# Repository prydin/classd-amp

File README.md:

# Class D Amplifier

Work in progress. Nothing to see here yet.

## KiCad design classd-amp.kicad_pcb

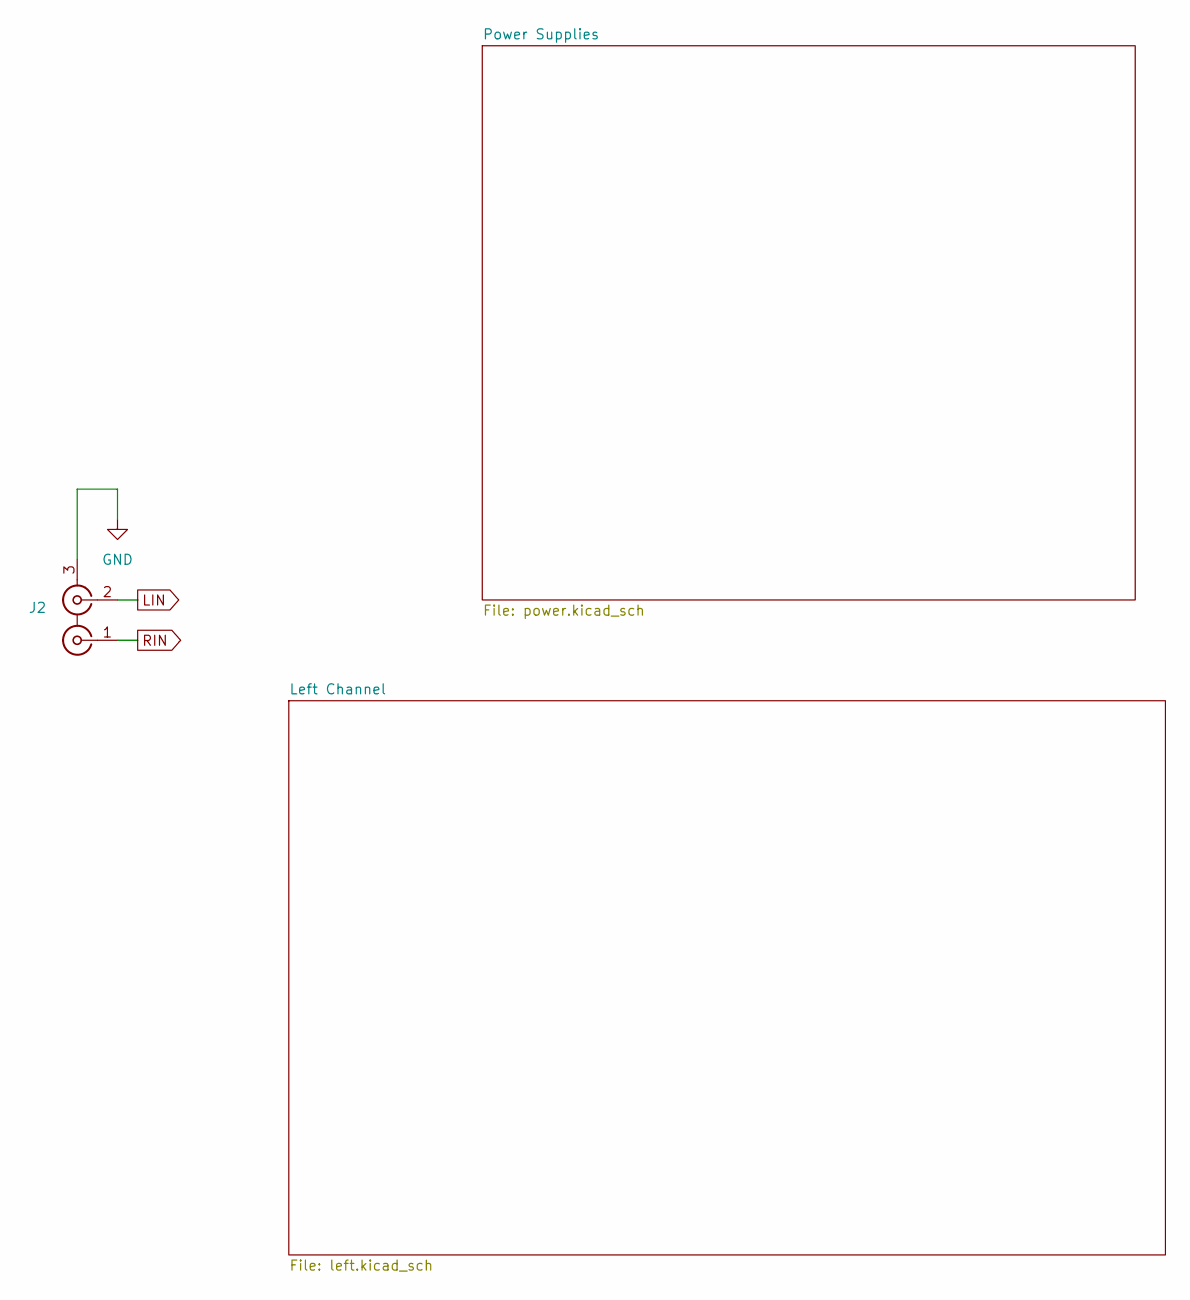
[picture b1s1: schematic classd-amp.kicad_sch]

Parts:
J2: Conn_Coaxial_x2; RCA_Stereo_Connector

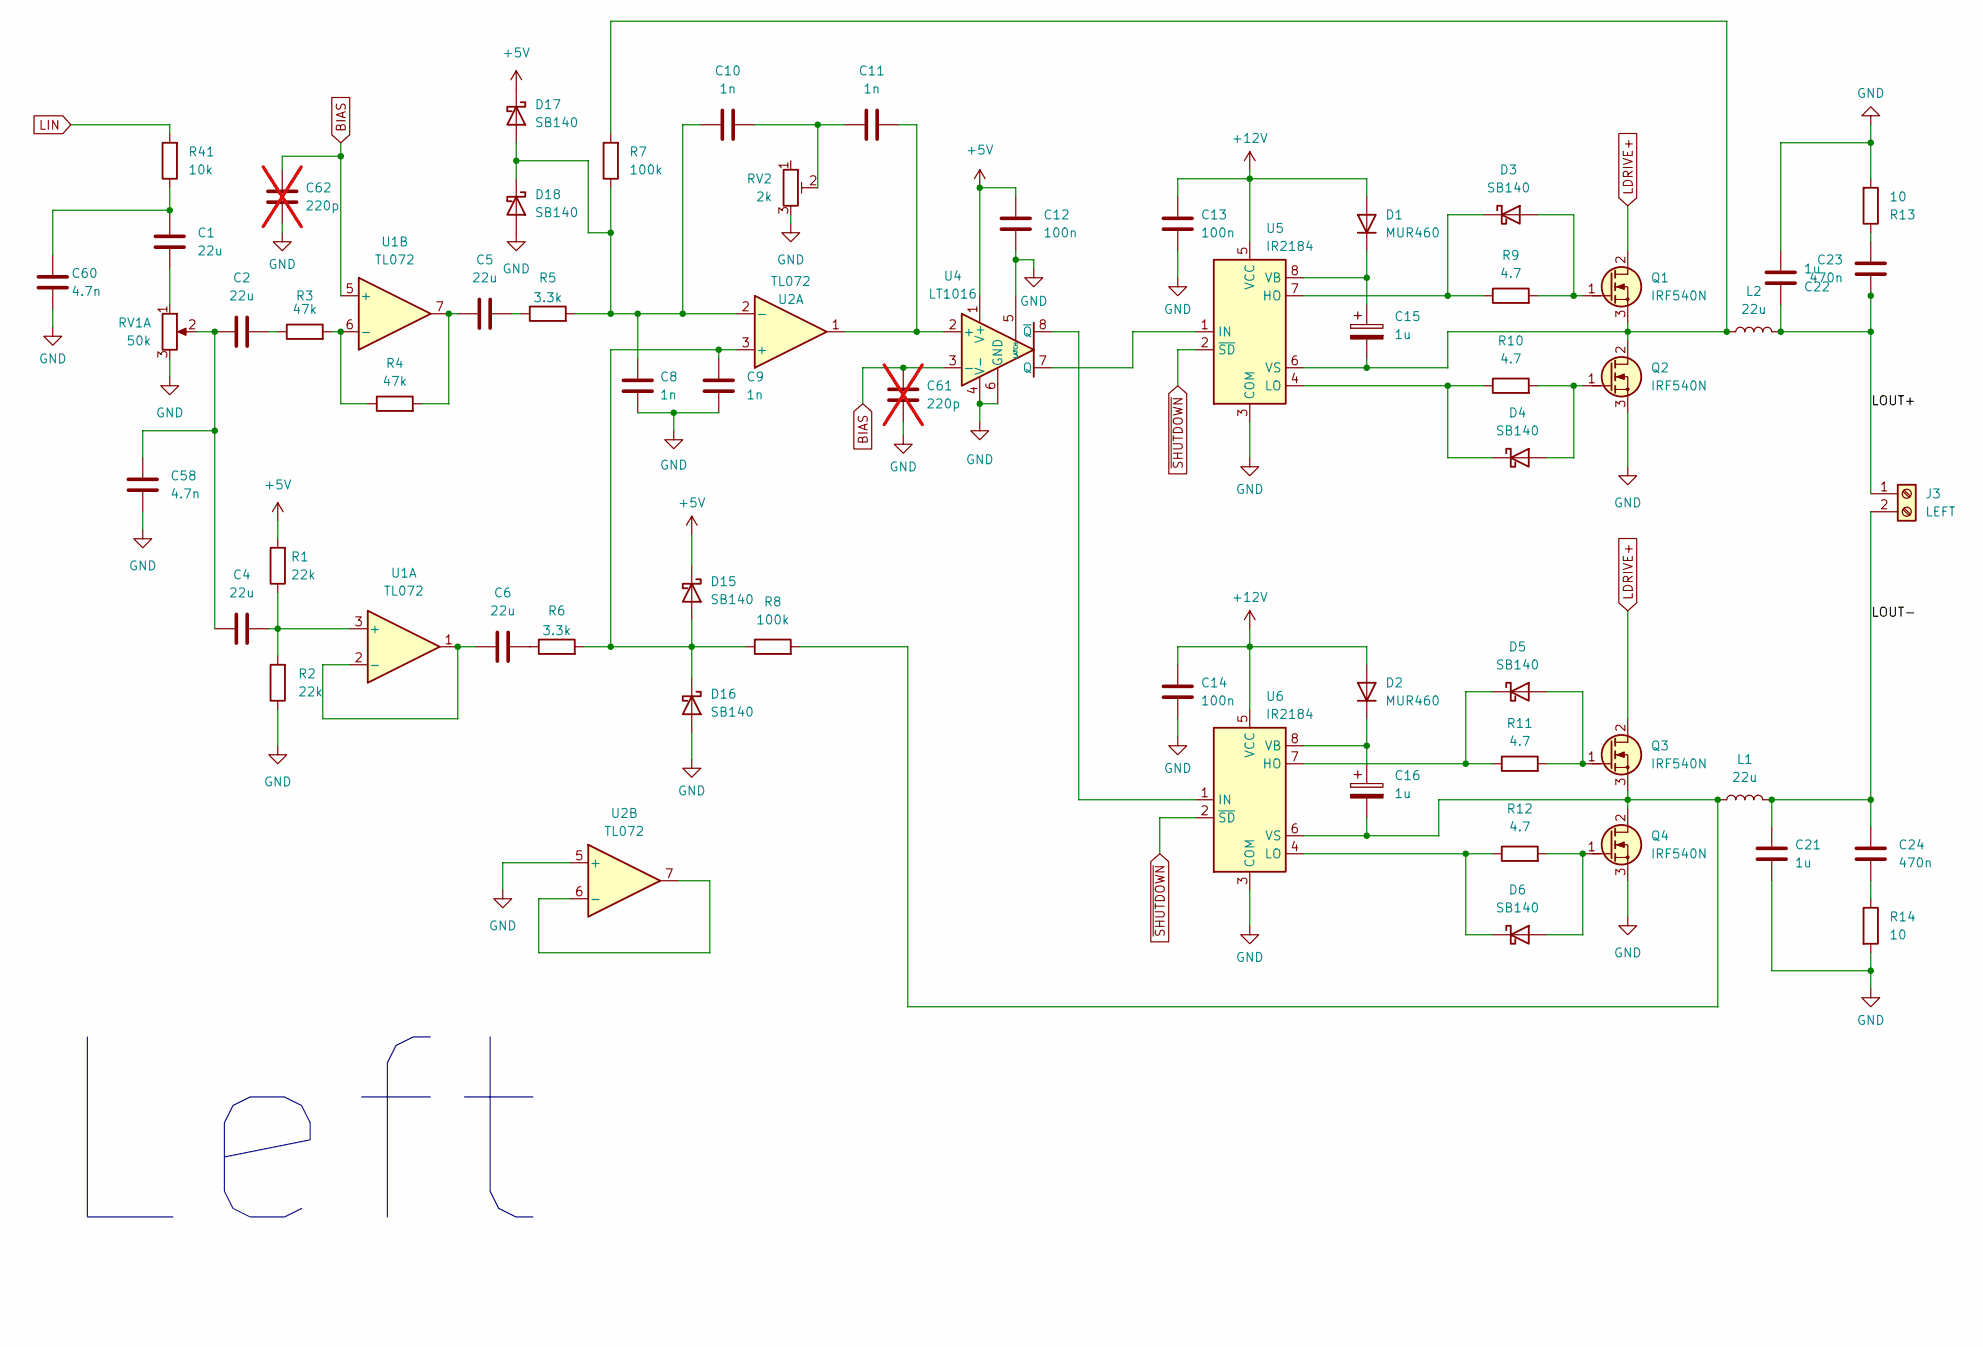
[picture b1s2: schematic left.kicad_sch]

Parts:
C1, C2, C4, C5, C6: 22u; CP_Radial_D8.0mm_P3.50mm
C8, C9, C10, C11: 1n; C_Disc_D4.7mm_W2.5mm_P5.00mm
C12, C13, C14: 100n; C_Disc_D3.4mm_W2.1mm_P2.50mm
C15, C16: 1u; CP_Radial_D4.0mm_P1.50mm
C21, C22: 1u; C_Rect_L18.0mm_W11.0mm_P15.00mm_FKS3_FKP3
C23, C24: 470n; C_Rect_L9.0mm_W3.8mm_P7.50mm_MKT
C58, C60: 4.7n; C_Disc_D3.4mm_W2.1mm_P2.50mm
C61, C62: 220p; C_Disc_D3.4mm_W2.1mm_P2.50mm; not fitted
D1, D2: MUR460; D_DO-41_SOD81_P10.16mm_Horizontal
D3, D4, D5, D6, D15, D16, D17, D18: SB140; D_DO-41_SOD81_P10.16mm_Horizontal
J3: LEFT; TerminalBlock_4Ucon_1x02_P3.50mm_Horizontal
L1, L2: 22u; L_Toroid_Vertical_L17.8mm_W8.1mm_P7.62mm_Bourns_5700
Q1, Q2, Q3, Q4: IRF540N; TO-220-3_Vertical
R1, R2: 22k; R_Axial_DIN0204_L3.6mm_D1.6mm_P7.62mm_Horizontal
R3, R4: 47k; R_Axial_DIN0204_L3.6mm_D1.6mm_P7.62mm_Horizontal
R5, R6: 3.3k; R_Axial_DIN0204_L3.6mm_D1.6mm_P7.62mm_Horizontal
R7, R8: 100k; R_Axial_DIN0204_L3.6mm_D1.6mm_P7.62mm_Horizontal
R9, R10, R11, R12: 4.7; R_Axial_DIN0204_L3.6mm_D1.6mm_P7.62mm_Horizontal
R13, R14: 10; R_Axial_DIN0614_L14.3mm_D5.7mm_P5.08mm_Vertical
R41: 10k; R_Axial_DIN0204_L3.6mm_D1.6mm_P7.62mm_Horizontal
RV1: 50k; PinHeader_1x03_P2.54mm_Vertical
RV2: 2k; Potentiometer_Runtron_RM-065_Vertical
U1, U2: TL072; DIP-8_W7.62mm_LongPads
U4: LT1016; DIP-8_W7.62mm_LongPads
U5, U6: IR2184; DIP-8_W7.62mm_LongPads

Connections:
+5V: C12.1, D15.1 (K), D17.1 (K), R1.2, U4.1 (V+); also elsewhere on the board
+12V: C13.1, C14.1, D1.2 (A), D2.2 (A), U5.5 (VCC), U6.5 (VCC); also elsewhere on the board
/Left Channel/LOUT+: C22.1, C23.1, J3.1, L2.2
/Left Channel/LOUT-: C21.1, C24.1, J3.2, L1.2
LDRIVE+: Q1.2 (D), Q3.2 (D); also elsewhere on the board
LIN: R41.2; also elsewhere on the board
unnamed: C1.1, C60.1, R41.1
unnamed: C1.2, RV1.1
unnamed: C2.1, R3.1
unnamed: C2.2, C4.2, C58.1, RV1.2
unnamed: C5.1, R4.2, U1.7
unnamed: C5.2, R5.1
unnamed: C6.2, R6.1
unnamed: C10.2, C11.1, RV2.2
unnamed: C23.2, R13.1
unnamed: C24.2, R14.1
unnamed: C15.1, D1.1 (K), U5.8 (VB)
unnamed: C16.1, D2.1 (K), U6.8 (VB)
unnamed: D3.2 (A), Q1.1 (G), R9.2
unnamed: D3.1 (K), R9.1, U5.7 (HO)
unnamed: D4.2 (A), Q2.1 (G), R10.2
unnamed: D4.1 (K), R10.1, U5.4 (LO)
unnamed: D5.2 (A), Q3.1 (G), R11.2
unnamed: D5.1 (K), R11.1, U6.7 (HO)
unnamed: D6.2 (A), Q4.1 (G), R12.2
unnamed: D6.1 (K), R12.1, U6.4 (LO)
unnamed: C9.1, D15.2 (A), D16.1 (K), R6.2, R8.1, U2.3 (+)
unnamed: C8.1, C10.1, D17.2 (A), D18.1 (K), R5.2, R7.1, U2.2 (-)
unnamed: C15.2, L2.1, Q1.3 (S), Q2.2 (D), R7.2, U5.6 (VS)
unnamed: C16.2, L1.1, Q3.3 (S), Q4.2 (D), R8.2, U6.6 (VS)
unnamed: C4.1, R1.1, R2.2, U1.3 (+)
unnamed: C6.1, U1.1, U1.2 (-)
unnamed: R3.2, R4.1, U1.6 (-)
unnamed: U2.6 (-), U2.7
unnamed: C11.2, U2.1, U4.2 (+)
unnamed: U4.7 (Q), U5.1 (IN)
unnamed: U4.8 (~Q), U6.1 (IN)
~SHUTDOWN: U5.2 (~SD), U6.2 (~SD); also elsewhere on the board

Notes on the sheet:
Left

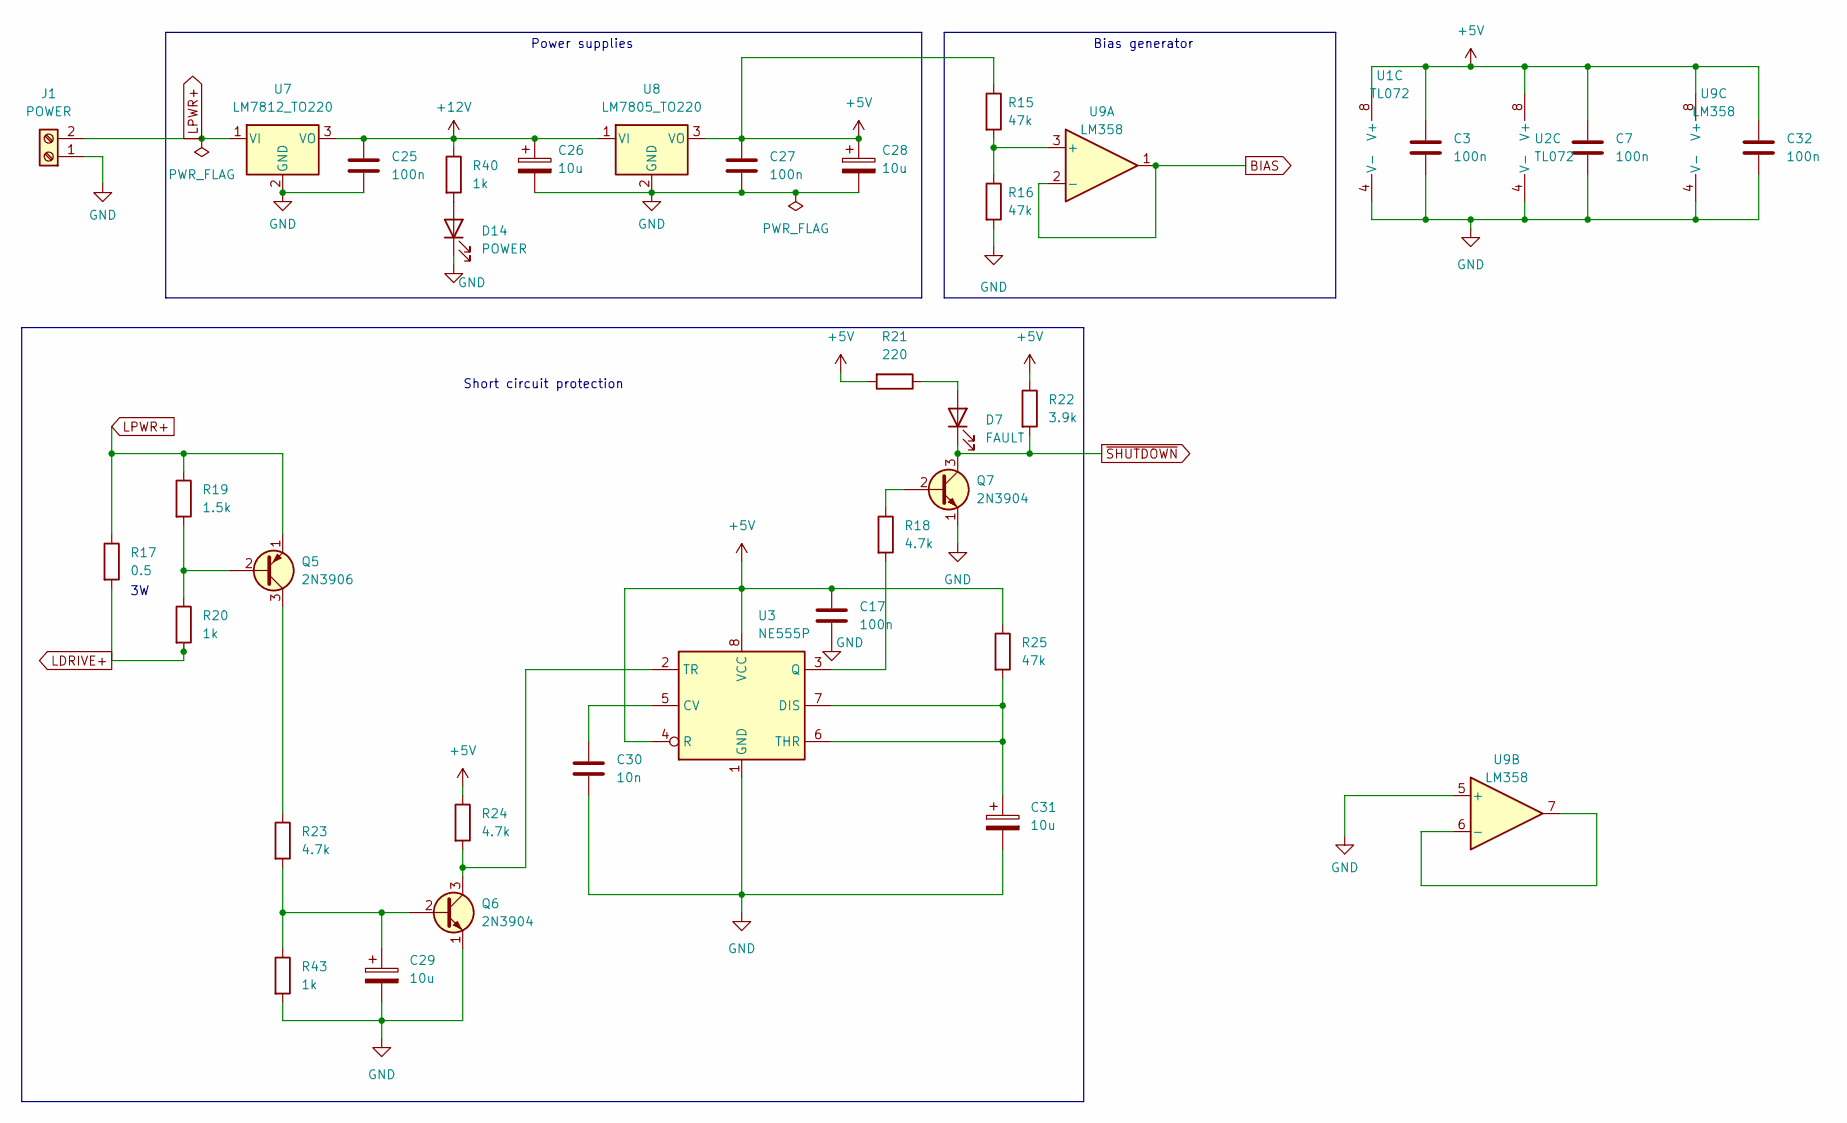
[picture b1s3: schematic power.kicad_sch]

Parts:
C3, C7, C17, C25, C27, C32: 100n; C_Disc_D3.4mm_W2.1mm_P2.50mm
C26, C28, C29, C31: 10u; CP_Radial_D4.0mm_P1.50mm
C30: 10n; C_Disc_D3.4mm_W2.1mm_P2.50mm
D7: FAULT; LED_D4.0mm
D14: POWER; LED_D4.0mm
J1: POWER; TerminalBlock_4Ucon_1x02_P3.50mm_Horizontal
Q5: 2N3906; TO-92_Inline
Q6, Q7: 2N3904; TO-92_Inline
R15, R16, R25: 47k; R_Axial_DIN0204_L3.6mm_D1.6mm_P7.62mm_Horizontal
R17: 0.5; R_Axial_DIN0922_L20.0mm_D9.0mm_P25.40mm_Horizontal
R18, R23, R24: 4.7k; R_Axial_DIN0204_L3.6mm_D1.6mm_P7.62mm_Horizontal
R19: 1.5k; R_Axial_DIN0204_L3.6mm_D1.6mm_P7.62mm_Horizontal
R20, R40, R43: 1k; R_Axial_DIN0204_L3.6mm_D1.6mm_P7.62mm_Horizontal
R21: 220; R_Axial_DIN0204_L3.6mm_D1.6mm_P7.62mm_Horizontal
R22: 3.9k; R_Axial_DIN0204_L3.6mm_D1.6mm_P7.62mm_Horizontal
U1, U2: TL072; DIP-8_W7.62mm_LongPads
U3: NE555P; DIP-8_W7.62mm
U7: LM7812_TO220; TO-220-3_Vertical
U8: LM7805_TO220; TO-220-3_Vertical
U9: LM358; DIP-8_W7.62mm_LongPads

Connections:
+5V: C3.1, C7.1, C17.1, C27.1, C28.1, C32.1, R15.1, R21.2, R22.1, R24.1, R25.1, U1.8 (V+), U2.8 (V+), U3.4 (R), U3.8 (VCC), U8.3 (VO), U9.8 (V+); also elsewhere on the board
+12V: C25.1, C26.1, R40.1, U7.3 (VO), U8.1 (VI); also elsewhere on the board
LDRIVE+: R17.2, R20.2; also elsewhere on the board
LPWR+: J1.2, Q5.1 (E), R17.1, R19.1, U7.1 (VI)
unnamed: D7.2 (A), R21.1
unnamed: D14.2 (A), R40.2
unnamed: Q5.2 (B), R19.2, R20.1
unnamed: Q5.3 (C), R23.1
unnamed: C29.1, Q6.2 (B), R23.2, R43.1
unnamed: Q6.3 (C), R24.2, U3.2 (TR)
unnamed: Q7.2 (B), R18.1
unnamed: C30.1, U3.5 (CV)
unnamed: C31.1, R25.2, U3.6 (THR), U3.7 (DIS)
unnamed: R18.2, U3.3 (Q)
unnamed: R15.2, R16.1, U9.3 (+)
unnamed: U9.6 (-), U9.7
~SHUTDOWN: D7.1 (K), Q7.3 (C), R22.2; also elsewhere on the board

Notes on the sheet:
Power supplies
Short circuit protection
Bias generator

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
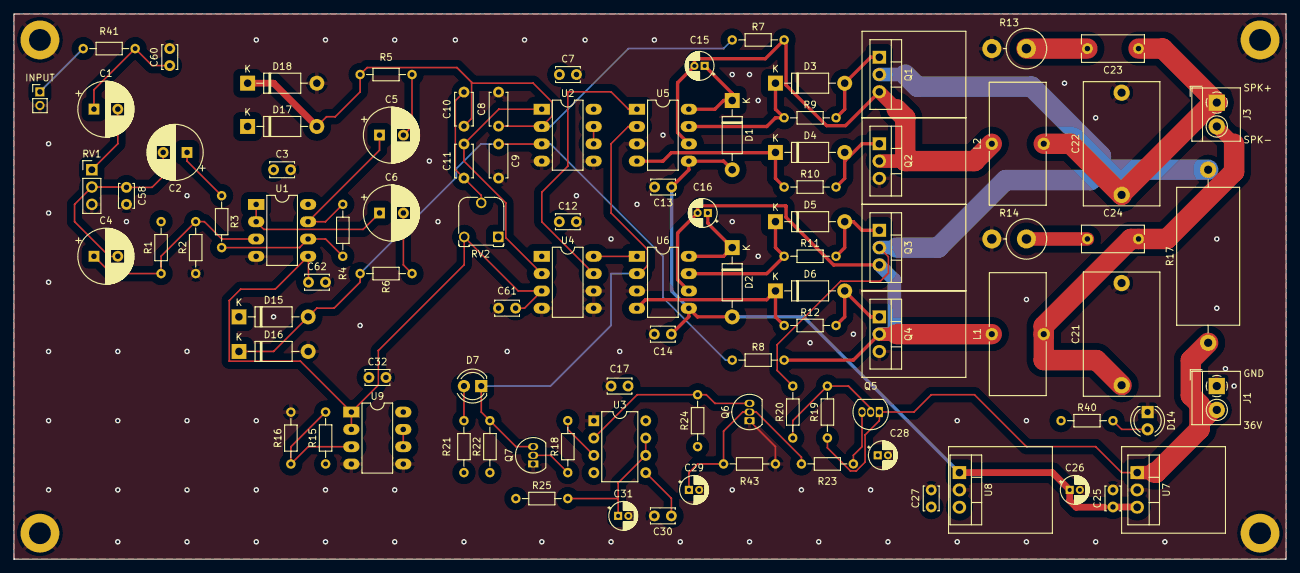
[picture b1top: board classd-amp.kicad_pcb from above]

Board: 4 copper layers, 186.7 x 80.0 mm, 96 parts (0 on the bottom side), 53 nets.

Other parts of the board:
INPUT: PinHeader_1x02_P2.00mm_Vertical

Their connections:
LIN: INPUT.1; also elsewhere on the board

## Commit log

2024-01-22 Added right channel
2024-01-25 First prototype
2024-02-06 Pre layer elimination
2024-02-09 Ver 1.1
2024-07-03 Salvaging PCB
2024-07-05 Recovered PCB
2024-07-12 Added spice files
